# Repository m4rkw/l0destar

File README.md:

# l0destar

[l0destar.com](https://l0destar.com) A fully open-source vehicle tracker - open hardware and open software.

Inspired by the [Geolink Opentracker](https://github.com/geolink/opentracker/) and the [Fortebit Polaris](https://www.fortebit.tech/polaris/), the goal is to build something that will last: a reference design for the best possible vehicle tracker that anyone can fab, modify, and host. Hardware and software are completely open and maintained as a community project.

## Status

Prototyping / design phase. The v2.1 layout worked on a bench, and v2.6 (CAN,
K-line and micro), v3.0, v3.1, v3.2 and v3.3 have since been built and bench
tested - see the test status table in each board's README. v3.4 is designed
but not yet built or tested.

<strong>All boards before v3.3 have a serious defect in the K-wire circuit
if the L wire is connected. If any of these prototypes are built the L wire
should not be connected to the vehicle as if it was ever externally shorted
to the 12V rail the l0destar device would be damaged.</strong> Luckily very
few people are going to care at all about this ancient protocol and even fewer
will ever need the L wire in normal use but it still bears mentioning as an
indication that these are very much prototypes and there may be other
undiscovered defects.

## Disclaimer

This is a prototype, not a product. Nothing here is validated, qualified or certified, the parts lists are examples rather than a verified BOM, and any test results are my own unverified bench observations. All responsibility for anything built from it rests with the person building and installing it.

**Before building, installing or relying on any of this, read the [full disclaimer](DISCLAIMER.md).**

## What it is

- **Mission** - the world's best fully open-source vehicle tracker, no profit motive. See [`MISSION.md`](MISSION.md).
- **Goals** - KiCad reference design, open enclosure CAD, open firmware and server, weeks of standby on a typical car battery, 1 Hz GNSS, LTE-M/NB-IoT, CAN + K-Line diagnostics, accelerometer-driven wake. Full list in [`GOALS.md`](GOALS.md).
- **Technology choices** - Nordic nRF9151 SiP (LTE-M/NB-IoT + GNSS), LT8609A buck, ASM330LHHX IMU, MCP2518FD + TCAN3414 CAN, TJA1027T K-Line. Rationale and trade-offs in [`TECHNOLOGY.md`](TECHNOLOGY.md).

## License

l0destar is multi-licensed by artifact type - permissive across the board:

| Artifact | License |
|---|---|
| Hardware design files | `CERN-OHL-P-2.0` |
| Firmware | `Apache-2.0` |
| Server-side software | `Apache-2.0` |
| Documentation, enclosure CAD, media | `CC-BY-4.0` |

Full text and rationale in [`LICENSE.md`](LICENSE.md); license bodies in [`LICENSES/`](LICENSES/).

## Contributing

Contributions are welcome. l0destar uses the [Developer Certificate of Origin](https://developercertificate.org/) rather than a CLA - every commit must carry a `Signed-off-by:` trailer (`git commit -s`). See [`CONTRIBUTING.md`](CONTRIBUTING.md) for PR expectations.

## Contact

- Bug reports and feature ideas: [GitHub Issues](https://github.com/m4rkw/l0destar/issues)
- Open-ended questions and design discussion: [GitHub Discussions](https://github.com/m4rkw/l0destar/discussions)
- Direct contact: [contact me](https://l0destar.com/contact.html)

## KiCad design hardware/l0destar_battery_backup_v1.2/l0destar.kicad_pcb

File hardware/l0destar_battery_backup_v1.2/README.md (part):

# l0destar battery backup v1.2

## Overview

- This is a prototype inline battery backup module for the l0destar vehicle
  tracker. It sits in the harness between the car and the tracker and holds
  the tracker's supply at ~9V from a single CR123A lithium primary cell when
  car power is cut
- It is designed to be hand-solderable (hot air required). Every active part
  is in a leaded package: MSOP-12, SOT-23, TSOT-23, SC70, DPAK
- The cell is a **non-rechargeable** primary in a board-mounted holder.
  Nothing on the board charges it. See [Why a primary cell](#why-a-primary-cell)
- Pin-compatible with the v3.4 tracker's 2x3 Micro-Fit harness: J1 takes the
  car harness, J2 goes to the tracker, the CAN/K-line pins pass straight
  through and ignition passes through a diode (S1D1)
- 4-layer 63.1 x 36.2 mm board, JLC04161H-7628 stack-up, four M2 mounting
  holes. PCB DRC is clean and schematic ERC has only the cosmetic
  `endpoint_off_grid` warnings

## Changes from v1.1

1. External pin assignments updated for v4.0 boards

## Disclaimer

This is a prototype, not a product. Nothing here is validated or certified,
the parts lists are examples rather than a verified BOM, and every number
below is a desk calculation from datasheets rather than a bench measurement -
repeat the testing yourself rather than taking any of it on trust.

I strongly recommend not using unbranded CR123 cells or buying them from less
reputable sources.

**Before building or installing anything from this repository, read the
[full disclaimer](../../DISCLAIMER.md).**

## Test status

| Item | Test | Result | Notes |
|---------|------|--------|-------|
| Input stage | 12V car input reverse polarity | PASSED | S2Z1 conducts forward into S2F1, which should clear |
| Input stage | Pass-through drop VCAR to PPTRACKER, tracker asleep | PASSED | v1.0 dropped ~0.5V here. Expected ~20 mV, the LTC4412 regulated forward drop |
| Input stage | Pass-through drop VCAR to PPTRACKER at 50 mA and 250 mA | PASSED | Expected ~20 mV; S2Q1 is 15 mΩ so the regulation sets it, not R<sub>DS(on)</sub> |
| Switchover | Boost enables when the car rail falls below ~10.06V | PASSED | S6U1 with the 6.8M/909k divider |
| Switchover | Boost disables when the car rail returns above ~11V | PASSED | Depends on the cell voltage through S6R38/S6R39, see [Notes](#notes) |
| Boost | 9.6V output at S4C14/S4C15 | PASSED | 1.202V x (1 + 909k/130k) = 9.61V; ~9V at J2 after S2D2 |
| Cell | Reversed cell is harmless | PASSED | Not physically possible to install the cell backwards |
| Cell | No current ever flows into the cell | PASSED | Ammeter in series with the cell with the car present and during handover |
| Wake pulse | IGN pulse at boost start, car ignition wire connected and off | PASSED | Failed on v1.0. Expected ~12V peak, above 8V for ~0.4 s, at J2 pin 5, with S1D1 blocking the car pulldown |
| Wake pulse | Car ignition reaches the tracker | PASSED | J2 pin 5 should be one S1B drop below J1 pin 5 with the key on |
| Wake pulse | Sleeping tracker wakes and raises `backup power` | PASSED | Needs firmware with `CONFIG_APP_BACKUP_SUPPLY=y` |
| Board | Parked drain from the car with the cell fitted | PASSED | ~15 µA on top of the tracker's own draw |

## Features

 - Inline between the car harness and the tracker; CAN/K-line pass straight
   through, ignition through S1D1
 - ~15 µA quiescent draw from the car in pass-through: ~13 µA LTC4412HV plus
   the ~1.6 µA sense divider
 - Same input protection parts as the tracker: 2A time-lag fuse, 33V TVS
   sized to ride out suppressed load dump
 - Reverse polarity protection
 - Ideal diode pass-through (LTC4412HV + P-channel FET) with a ~20 mV drop
   down to sleep current
 - Synchronous boost (LTC3122) with true output disconnect: the backup rail
   is 0V while the car is present, so the cell is only ever loaded during a
   cut
 - Nanopower comparator switchover (TLV3012, 2.8 µA) running straight from
   the cell: takes over below ~10.06V on the car rail
 - No cell lockout: the boost runs the cell until it can't. It's a
   consumable primary, so there is nothing to protect
 - Ignition wake pulse: a cut wakes a sleeping tracker immediately instead of
   at its next timed wake, and the tracker reports the cut
 - Estimated runtime on a 1500 mAh CR123A: ~200 days idle, ~58 days
   reporting hourly, ~19 days reporting every 15 minutes
 - 3D-printable two-part enclosure with the cell accessible under the lid

## Why a primary cell

A non-rechargeable cell rather than a rechargeable pack, for three reasons:

- No rechargeable 18650-format cell is rated for storage in a sun-parked car.
  The binding limit is storage temperature (+45 °C at best for Li-ion and LFP;
  +20 °C beyond three months for LTO) and a parked car reaches ~70 °C cabin
  air. A CR123A is rated to +60/+70 °C
- Cycle life is not worth paying for. The backup cycles a handful of times a
  year
- A primary turns silent ageing into an event. The boost regulates its output,
  so the tracker cannot see cell voltage - a rechargeable's calendar fade would
  be invisible until a real theft tested it. The only thing that consumes a
  primary is a power cut the tracker already alerts on, so *"did it get
  used?"* is answered in the server's alert log

The cell is a consumable. A `backup power` alert that runs for a long time
means the cell needs replacing, since it does not recover. Taking the cell
out is the storage mode.

### Ignition wake pulse

A sleeping tracker has three wake sources: its timer, the accelerometer and
ignition-present. A power cut touches none of them, so on its own it would be
found at the next timed wake. The module therefore fakes ignition for a
moment when it takes over.

The tracker's wake is level-triggered and the firmware latches it, so the
pulse only has to trip the interrupt. On an ignition wake the firmware reads
the rail first: in the backup band it is the module's pulse, so the unit
reports at once with the `backup power` alert and goes back to sleep.

The car holds its ignition wire at ground when the key is off, which sank
the pulse on v1.0. S1D1 sits in series between the car's ignition (J1 pin 5)
and the tracker's (J2 pin 5) so the pulse only drives the tracker's input.
The cost is one silicon diode drop on the ignition signal the tracker sees.

Limits: a second cut within the ~40 s VBOOST decay gives no pulse and falls
back to the timed wake.

## Board configuration

### Connectors

Both connectors are the tracker's Molex Micro-Fit 3.0 2x3 (43045-0600) with
the v3.4 pinout. J1 is the car harness, J2 goes to the tracker.

| Pin | J1 (car) | J2 (tracker) | Notes |
|-----|----------|--------------|-------|
| 1 | SPARE | SPARE | Unused by v3.4, not connected on this board |
| 2 | GND | GND | |
| 3 | CAN\_H / K | CAN\_H / K | Passed straight through |
| 4 | +12V | +12V (PPTRACKER) | Car through the ideal diode, or ~9V from the boost on backup |
| 5 | IGN | IGN | Through S1D1 (one diode drop); the wake pulse is injected on the J2 side |
| 6 | CAN\_L / L | CAN\_L / L | Passed straight through |

### Firmware

The tracker needs `CONFIG_APP_BACKUP_SUPPLY=y`. With it, a supply between
`CONFIG_APP_BACKUP_MIN_MV` (8500) and `CONFIG_APP_BACKUP_MAX_MV` (9700) with
the ignition off is treated as backup power rather than a flat car battery:
timed reports keep going, the 11.8V power-off and 12.0V sleep-safety rules
are bypassed, a `backup power` alert is raised once and a `car power
restored` alert when the rail comes back. Without the module a car battery in
that band is flat, so leave it off on trackers that do not have one.

### Cell

The board carries a Keystone 1051 CR123A holder and nothing else as a cell
input. Fit a CR123A from one of the three big brands (Energizer 123 /
EL123AP, Panasonic CR123A, Duracell DL123A): all are high-rate Li-MnO2 cells,
1500-1550 mAh, rated for the ~130 mA typical / ~250 mA worst-case bursts the
boost draws. Mark polarity on the silk and the lid; a reversed cell is
harmless but gives no backup.

Other primary chemistries (a 4.1V Tadiran TLM for installs above 60 °C, a
C-size Li-SOCl2 for long runtime) are **not** stuffing options on this board:
neither fits the CR123A holder, a 4.1V cell needs the comparator's supply
range and the boost input checked, and Li-SOCl2 wants a depassivation
bleed. Either is a sheet 3 change.

## Notes

 - **Nothing may ever charge the cell.** Do not add any path from VBOOST,
   PPTRACKER or VCAR to VBAT. If the LM66100 is ever replaced, the
   replacement must block reverse current
 - The LTC3122's exposed pad is PGND. Solder it
 - The tracker's flex-crack rule applies to every 1210 ceramic on this board
   (S2C5, S2C6, S4C14, S4C15): soft-termination parts only, kept away from
   board edges and mounting holes
 - S4R19 (boost FB top) is the one anti-sulfur resistor that matters: open, the
   LTC3122 runs to its ceiling, the same failure as the tracker buck's top
   resistor. S6R33 uses the same part for convenience. Everything else is
   plain thick film; use a non-sulfur foam under the lid over the cell
 - S2D2 and S5D3 must stay glass-passivated silicon (S1B), not Schottky. The
   wake pulse depends on VBOOST resting near 0V while the car is present, and
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
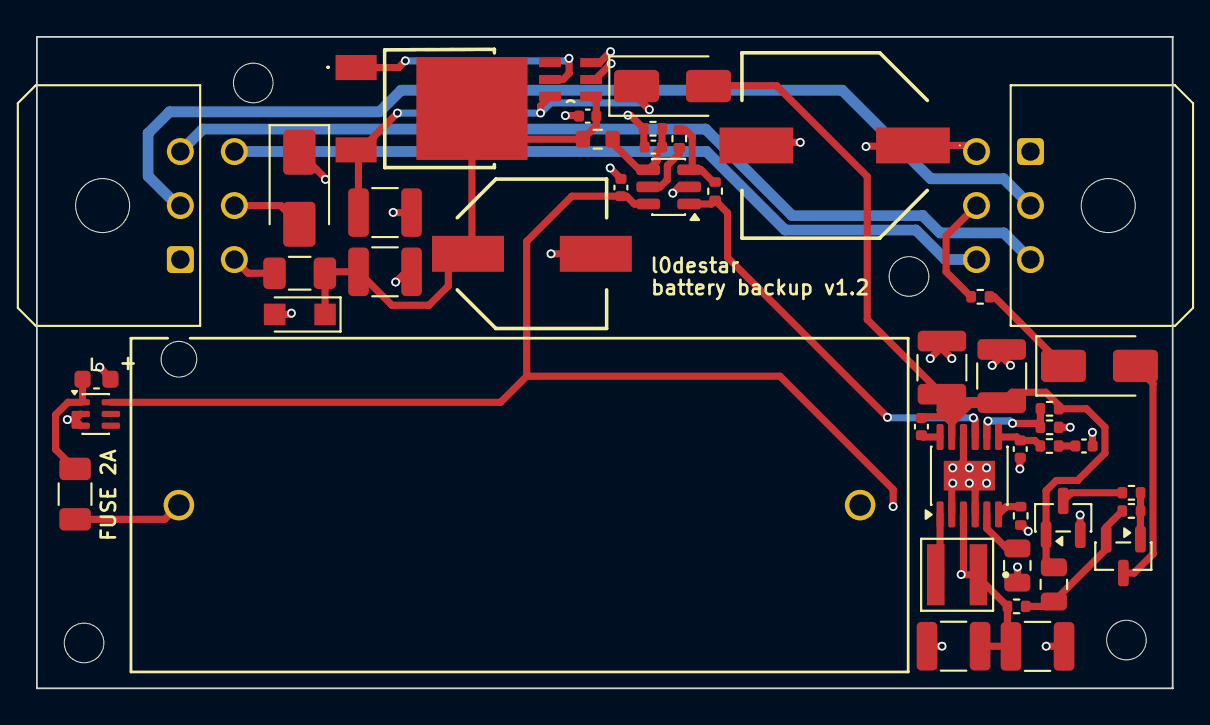
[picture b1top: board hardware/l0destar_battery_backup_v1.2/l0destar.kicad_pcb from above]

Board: 4 copper layers, 63.1 x 36.2 mm, 50 parts (0 on the bottom side), 30 nets.

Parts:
S1D1, S2D2, S5D3: S1B; D_SMA
S1H1, S1H2, S1H3, S1H4: MountingHole; MountingHole_2.2mm_M2
S1J1: Car harness; Molex_Micro-Fit_3.0_43045-0600_2x03_P3.00mm_Horizontal
S1J2: Tracker harness; Molex_Micro-Fit_3.0_43045-0600_2x03_P3.00mm_Horizontal
S2C1, S4C9, S6C2: 0402 100nF 50V 10% X7R; C_0402_1005Metric
S2C2: 47uF 63V - EEH-ZC1J470P; EEH_ZC1J470P
S2C4: 82uF 63V - HHXC630ARA820MJA0G; HHXC630ARA820MJA0G
S2C5, S2C6, S4C14, S4C15: 1210 10uF 50V X7R SOFT-TERM; C_1210_3225Metric
S2F1, S3F1: 0407002.WRA; Fuse_1206_3216Metric
S2Q1: SQD50P06-15L_GE3; SQD50P06-15L_GE3_tight
S2U1: LTC4412HVIS6PBF
S2Z1: PTVS33VS1UTR,115; Nexperia_CFP3_SOD-123W
S3BT1: CR123A; 1051_KEY
S3C1: 0603 2.2uF 25V 10% X7R; C_0603_1608Metric
S3U1: LM66100DCKR; SOT-363_SC-70-6
S4C7, S4C8: 1210 47uF 10V 20% X7R; C_1210_3225Metric
S4C11: 0402 560pF 50V 5% C0G/NP0; C_0402_1005Metric
S4C12: 0402 10pF 50V C0G/NP0; C_0402_1005Metric
S4C13, S5C17: 0805 4.7uF 50V 10% X7R; C_0805_2012Metric
S4L1: 2.2uH XFL4020-222MEC; IND_XFL4020-222ME
S4R14: 0402 57.6K 1%; R_0402_1005Metric
S4R18: 0402 200K 1%; R_0402_1005Metric
S4R19, S6R33: 0402 909K 1% ANTI-SULFUR AEC-Q200; R_0402_1005Metric
S4R20: 0402 130K 1%; R_0402_1005Metric
S4U5: LTC3122EMSE#PBF; MSOP-12-1EP_3x4.039mm_P0.65mm_EP1.651x2.845mm
S5Q6: 2N7002; SOT-23
S5Q7: BC856B; SOT-23
S5R21: 0402 10K 5%; R_0402_1005Metric
S5R22, S5R24, S5R25, S6R39: 0402 1M 1%; R_0402_1005Metric
S6C1: 0402 100pF 50V 5% C0G/NP0; C_0402_1005Metric
S6R32: 0603 6.8M 1%; R_0603_1608Metric
S6R38: 0402 47K 5%; R_0402_1005Metric
S6U1: TLV3012AIDBVR; SOT-23-6

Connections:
CAN_H: S1J1.3, S1J2.3
CAN_L: S1J1.6, S1J2.6
EN_BOOST: S4U5.9 (SD), S6R39.1, S6U1.1 (OUT)
GND: S1J1.1, S1J2.1, S2C1.2, S2C2.2 (-), S2C4.2 (-), S2C5.2, S2C6.2, S2U1.2 (GND), S2U1.3 (CTL), S2Z1.2 (A), S3BT1.2, S3C1.2, S3U1.2 (GND), S3U1.3 (~CE), S4C7.2, S4C8.2, S4C11.2, S4C12.2, S4C13.2, S4C14.2, S4C15.2, S4R14.2, S4R20.2, S4U5.2 (PGND), S4U5.4 (PWM/SYNC), S4U5.10 (SGND), S4U5.13 (EP), S5Q6.2 (S), S6C1.2, S6C2.2, S6R33.2, S6U1.2 (V-)
IGN: S1D1.1 (K), S1J2.5, S5R21.2
IGN_CAR: S1D1.2 (A), S1J1.5
KWIRE_K: S1J1.2, S1J2.2
unnamed: S2Q1.1 (G), S2U1.5 (GATE)
unnamed: S3BT1.1, S3F1.1
unnamed: S3C1.1, S3F1.2, S3U1.1 (VIN)
unnamed: S4C11.1, S4R18.2
unnamed: S4C9.1, S4U5.12 (CAP)
unnamed: S4R19.2, S4R20.1, S4U5.8 (FB)
unnamed: S4R14.1, S4U5.6 (RT)
unnamed: S4L1.2, S4U5.1 (SW)
unnamed: S4C12.1, S4R18.1, S4U5.7 (VC)
unnamed: S4C13.1, S4U5.5 (VCC)
unnamed: S5D3.2 (A), S5Q7.3 (C)
unnamed: S5D3.1 (K), S5R21.1
unnamed: S5Q6.3 (D), S5R24.2
unnamed: S5Q7.1 (B), S5R24.1, S5R25.2
unnamed: S5C17.1, S5Q7.2 (E), S5R22.2, S5R25.1
unnamed: S6R38.2, S6R39.2, S6U1.3 (IN+)
unnamed: S6C1.1, S6R32.2, S6R33.1, S6U1.4 (IN-)
unnamed: S6R38.1, S6U1.5 (REF)
PP12V: S1J1.4, S2F1.1
PPTRACKER: S1J2.4, S2C4.1 (+), S2C5.1, S2D2.1 (K), S2Q1.3 (S), S2U1.6 (SENSE)
VBAT: S3U1.6 (VOUT), S4C7.1, S4C8.1, S4L1.1, S4U5.3 (VIN), S5R22.1, S6C2.1, S6U1.6 (V+)
VBOOST: S2D2.2 (A), S4C9.2, S4C14.1, S4C15.1, S4R19.1, S4U5.11 (VOUT), S5C17.2, S5Q6.1 (G)
VCAR: S2C1.1, S2C2.1 (+), S2C6.1, S2F1.2, S2Q1.2 (D), S2U1.1 (VIN), S2Z1.1 (K), S6R32.1

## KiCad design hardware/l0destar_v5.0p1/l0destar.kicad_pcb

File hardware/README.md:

# l0destar hardware

**Before building, installing or relying on any of this, read the [project disclaimer](../DISCLAIMER.md).**

## Overview

KiCad PCB designs for the l0destar vehicle tracker. All boards are built around
the Nordic nRF9151 for LTE-M/GPS and share a common set of subsystems: 12V
automotive power input, INA228 voltage monitoring, ignition sensing, and an
accelerometer/IMU.

**THESE SHOULD NOT BE CONSIDERED FINISHED PRODUCTS. SOME OF THEM HAVEN'T BEEN
TESTED AT ALL. USE ENTIRELY AT YOUR OWN RISK.**

**SOME OF THESE HAVE KNOWN DEFECTS DETAILED IN THEIR README**

Prototypes here are currently being tested and evaluated, there are typically a
few in the pipeline at any given time. Older boards no longer being tested are
moved into the [archive](archive/).

## PCB designs

### v3.1 - input resilience, hardened antenna feed, aux rail fault detection

- **[l0destar v3.1](l0destar_v3.1/)** - v3.0 with more robust input protection
  (sized for ISO 7637-2 pulse 2a), auxiliary power rail sensing/fault
  detection, and a hardened antenna feed with 15R series resistance and ESD
  protection. Same footprint as v3.0. Tested - 130 µA quiescent, all major
  subsystems passed.

### v3.2 - MCU over-voltage protection

- **[l0destar v3.2](l0destar_v3.2/)** - v3.1 plus hardware over-voltage
  protection that disconnects the module supply within microseconds of a
  regulator fault (self-recovering, no firmware dependency, ~10 µA), and I2C
  bus hardening against LTE TX bursts (stronger pull-ups, 100pF filter caps
  on SDA/SCL, series jumper/ferrite on the accelerometer supply).

  Tested successfully: <a href="https://www.youtube.com/watch?v=6-iVvQPaaeg">OVP scope test</a>.
  134 µA quiescent with firmware 0.4.26 (140.8 µA before it moved the sleep
  wake interrupts off the GPIOTE channels).

### v3.3 - L-line defect fix

- **[l0destar v3.3](l0destar_v3.3/)** - fixes the L-line short-to-battery
  defect present in v3.0-v3.2 (pulldown current limited to 90 mA via an
  AL5809-90, gate-fault current into the nRF limited) and adds L-line fault
  sensing so a 12V short can be detected. Buck converter tuned to shut off
  cleanly below ~4.3V and restart only above ~5.6V to avoid flapping. Built and
  bench tested: 146.2 µA quiescent as built, 43.7 µA with the accelerometer's
  NC pads scraped off.

### v3.4 - accelerometer fix

- **[l0destar v3.4](l0destar_v3.4/)** - v3.3 with the accelerometer's NC pins
  left unconnected (grounded on v3.0-v3.3, which kept the part out of its
  low-power state), the buck enable divider made optional, test points added
  and a TCAN3414DR CAN transceiver specified. Not yet built or tested; ~35.5 µA
  quiescent expected at 12V.

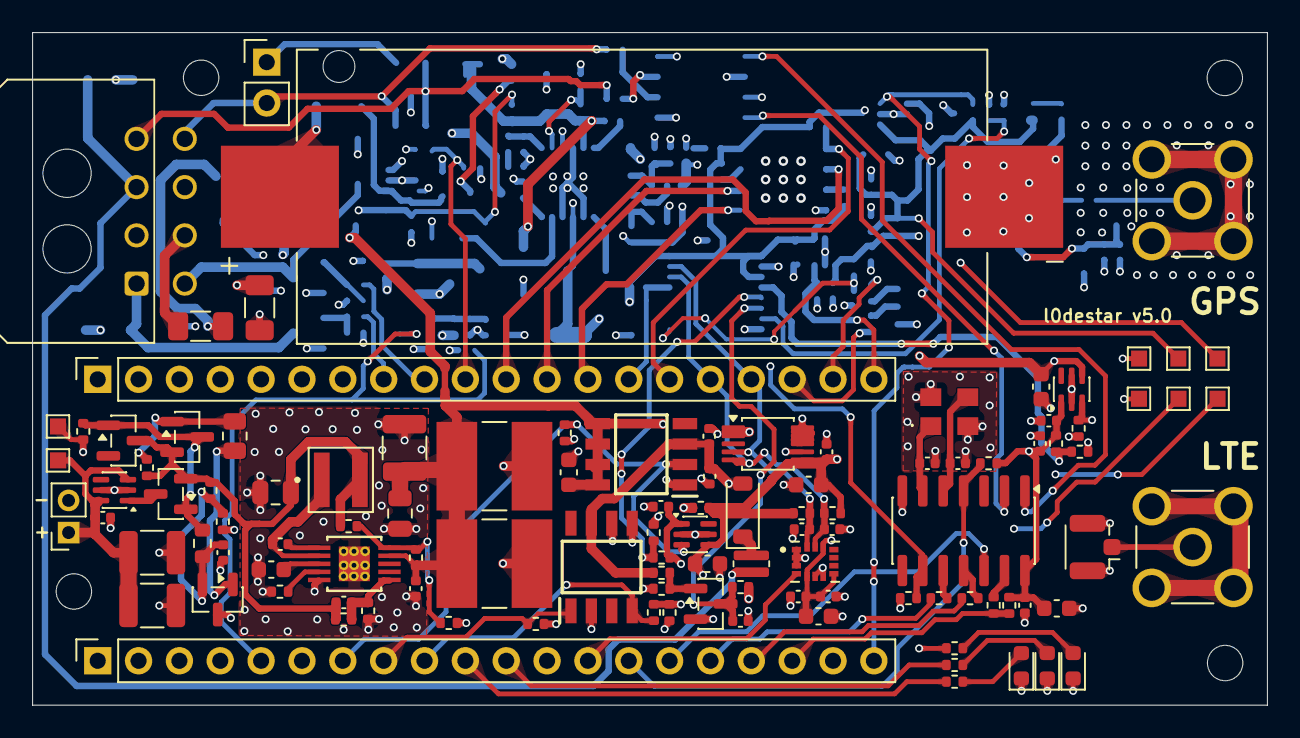
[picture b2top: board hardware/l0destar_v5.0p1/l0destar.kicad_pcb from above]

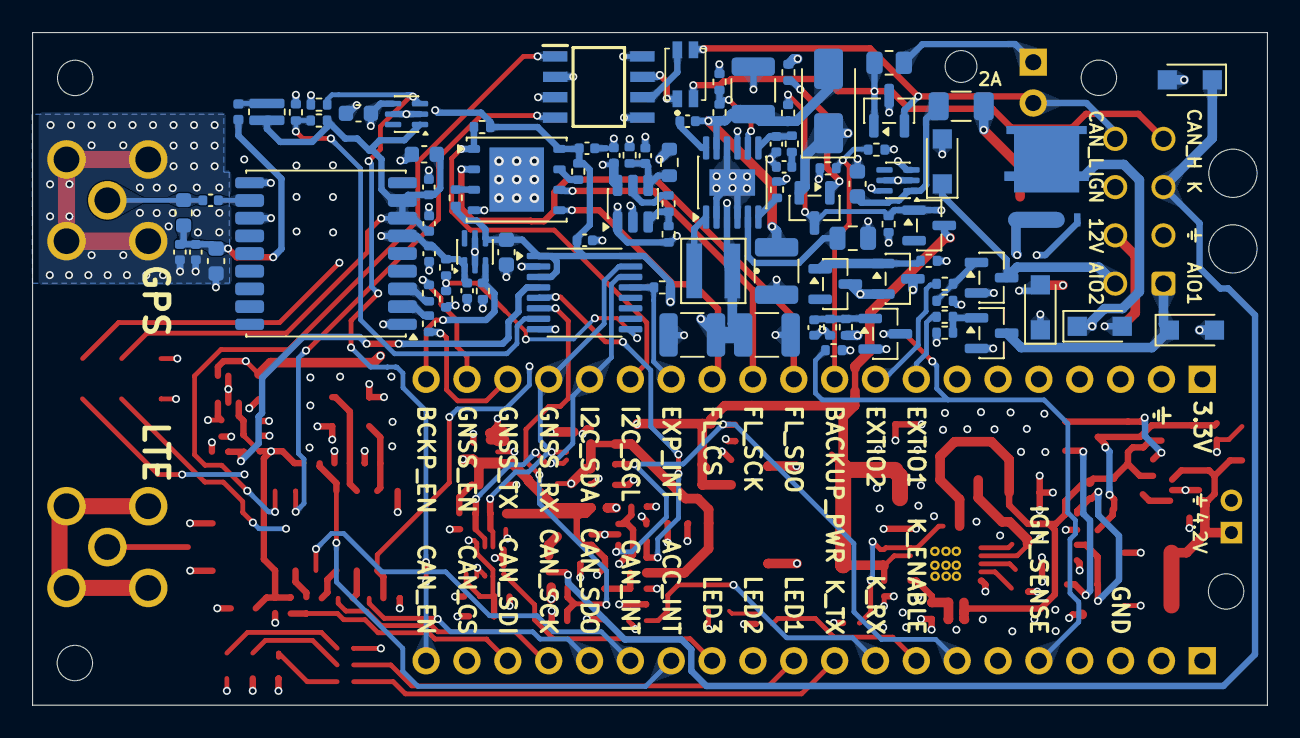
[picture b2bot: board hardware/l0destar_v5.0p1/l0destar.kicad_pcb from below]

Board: 4 copper layers, 76.8 x 41.8 mm, 202 parts (89 on the bottom side), 112 nets.

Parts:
H1, H2, H3, H4: MountingHole; MountingHole_2.2mm_M2
S1C1, S3C2, S4C1, S6C1, S6C8, S7C2, S7C4, S7C9, S8C1, S8C3, S9C1, S9C4, S10C1, S16C2, S16C4, S16C5, S17C1, S19C9, S20C2, S22C1: 0402 100nF 50V 10% X7R; C_0402_1005Metric
S1J1: Main connector; Molex_Micro-Fit_3.0_43045-0800_2x04_P3.00mm_Horizontal
S1J2: Conn_01x20_Socket; MakerDiary_nRF9151_ConnectKit_PinHeader_1-20_tight
S1J3: Conn_01x20_Socket_21-40; MakerDiary_nRF9151_ConnectKit_PinHeader_21-40_tight
S1J4: +; MakerDiary2PinHeader
S1R1, S1R2: 0402 1.8K 1%; R_0402_1005Metric
S1R3, S1R4, S1R5, S2R3, S2R4, S7R3, S7R6, S7R7, S7R8, S7R10, S10R6, S16R1, S16R4, S21R2, S21R4: 0402 100K 5%; R_0402_1005Metric
S2C1, S2C2: 47uF 2220 50V 20% X7R; CAPC6050X550N
S2C3: 10uF 1210 50V 10% X7R SOFT TERMINATION; C_1210_3225Metric
S2D1, S2D3, S11D1: BZX84C15; SOT-23
S2D2, S2D4, S10D2, S21D1, S21D2: PTVS33VS1UTR,115; Nexperia_CFP3_SOD-123W
S2D5: S1B; D_SMA
S2F1, S2F2, S18F1: 0407002.WRA; Fuse_1206_3216Metric
S2Q1, S2Q3, S11Q1: SQ2361CES-T1_BE3; SOT-23
S2Q2: SQJ457EP-T1_BE3; POWERPAK-SO-8-4
S2R1, S7R4, S7R9, S7R11, S16R5: 0402 1M 5%; R_0402_1005Metric
S2R2, S20R41: 0402 2.2M 1%; R_0402_1005Metric
S3C1, S6C2, S7C1, S7C3, S7C8, S15C4, S16C1, S16C3, S18C1: 0603 2.2uF 25V 10% X7R; C_0603_1608Metric
S3U1: INA238; TSSOP-10_3x3mm_P0.5mm
S4Q1, S7Q1, S21Q1, S21Q2: 2N7002; SOT-23
S4R1, S7R5: 0402 180K 5%; R_0402_1005Metric
S4R2, S4R3: 0402 56K 5%; R_0402_1005Metric
S6C3, S19C13: 0805 4.7uF 50V 10% X7R; C_0805_2012Metric
S6C4, S19C12: 0402 10pF 50V C0G/NP0; C_0402_1005Metric
S6C5: 0805 22uF 10V 20% X7R; C_0805_2012Metric
S6L1: XFL4020-222ME; IND_XFL4020-222ME
S6R1: 0402 18.2K 1%; R_0402_1005Metric
S6R2: 0402 226K 1% ANTI-SULFUR AEC-Q200; R_0402_1005Metric
S6R3, S11R5: 0402 1M 1% ANTI-SULFUR AEC-Q200; R_0402_1005Metric
S6R4: 0402 0R JUMPER OR 1M 1% ANTI-SULFUR AEC-Q200; R_0402_1005Metric
S6R5: DNP 0402 243K 1% ANTI-SULFUR AEC-Q200; R_0402_1005Metric
S6R6: DNP 0402 3.92M 1%; R_0402_1005Metric
S6U1: LT8609AIMSE_PBF; LT8609AIMSE_WITH_GROUND_VIAS
S7C5, S7C7: 0402 1nF 50V 10% X7R; C_0402_1005Metric
S7C6: 0603 220nF 50V 10% X7R; C_0603_1608Metric
S7U1, S7U2, S7U4, S16U1: SiP32431DR3; SOT-363_SC-70-6
S7U3: ITS4060SSJNXUMA1
S8C2, S9C5: 0603 10uF 10V 20% X7R; C_0603_1608Metric
S8C4, S8C5, S15C2, S20C1: 0402 100pF 50V 5% C0G/NP0; C_0402_1005Metric
S8R1: 0402 FB BLM15AG601SH1D; R_0402_1005Metric
S8U1: ASM330LHHXTR; XDCR_ASM330LHHXTR
S9C2, S9C3: 0402 27pF 10V 5% C0G/NP0; C_0402_1005Metric
S9D1: NUP2105L; SOT-23
S9FL1: ACT1210-101-2P-TL00; ACT12101012PTL00_tight
S9J1: Conn_01x02_Pin; PinHeader_1x02_P2.54mm_Vertical_Tight
S9R1, S9R2, S9R4, S10R1, S10R2, S17R1, S17R2, S17R3, S20R40, S22R1: 0402 10K 5%; R_0402_1005Metric
S9R3: 0805 120R 5% 0.5W; R_0805_2012Metric
S9R5, S13R1, S13R2, S13R3, S16R2, S16R3, S21R1, S21R3: 0402 1K 5%; R_0402_1005Metric
S9R6, S9R7: 0402 220R 5%; R_0402_1005Metric
S9U1: TCAN3414DR; SOIC127P600X175-8N
S9U2: MCP2518FD-xQBB; SOIC-14_3.9x8.7mm_P1.27mm
S9Y1: ECS-400-18-33-JGN-TR3; ECS4001833JGNTR3
S10D1: 1N4148W; D_SOD-123
S10R3: 0508 510R 5% 1W; R_0508_1220Metric_WideTerminal_Tight
S10U1: TJA1027T_20,118; TJA1027T_20_118
S11C1, S11C2, S19C7, S19C8: 1210 47uF 10V 20% X7R; C_1210_3225Metric
S11C3: 0402 3.3pF 50V C0G/NP0 +/- 0.25pF; C_0402_1005Metric
S11Q2: BC856BLT1G; SOT-23
S11R1: 0402 10K 1%; R_0402_1005Metric
S11R2, S20R39: 0402 1M 1%; R_0402_1005Metric
S11R3: 0603 33M 5%; R_0603_1608Metric
S11R4: 0805 15K 1% ANTI-SULFUR AEC-Q200; R_0805_2012Metric
S11R6: 0402 1.05M 1%; R_0402_1005Metric
S11U1: LM66100DCK; SOT-363_SC-70-6
S11U2: ATL431BQDBZR; SOT-23
S12TP1: GND; TestPoint_Pad_1.0x1.0mm
S12TP2: 4.2V protected; TestPoint_Pad_1.0x1.0mm
S12TP3: 3.3V; TestPoint_Pad_1.0x1.0mm
S12TP4: 3.3V GNSS BCKP; TestPoint_Pad_1.0x1.0mm
S12TP5: 3.3V CAN; TestPoint_Pad_1.0x1.0mm
S12TP6: 3.3V K; TestPoint_Pad_1.0x1.0mm
S12TP7: 12V K; TestPoint_Pad_1.0x1.0mm
S13D1, S13D2, S13D3: Wurth 150060RS86000; LED_0603_1608Metric
S15C1: 0402 47pF 50V 5% C0G/NP0; C_0402_1005Metric
S15C3: 0402 10nF 50V 5% C0G/NP0; C_0402_1005Metric
S15FB1: 0402 600R 0.5A 25%; L_0402_1005Metric
S15J2: GPS_SMA; SAMTEC_SMA-J-P-H-RA-TH1_centrepin
S15J3: GSM_UFL; U.FL_Hirose_U.FL-R-SMT-1_Vertical
S15J4: GSM_SMA; SAMTEC_SMA-J-P-H-RA-TH1_centrepin
S15L1: LQW18AN68NJ00D; L_0603_1608Metric
S15R1: 0508 1W 5% 15R; R_0508_1220Metric_WideTerminal_Tight
S16TP1: 3.3V GNSS; TestPoint_Pad_1.0x1.0mm
S16U2: MAX-M10S; ublox_MAX
S17U1: MX25R6435FZNIL0; WSON-8-1EP_6x5mm_P1.27mm_EP3.4x4mm_no_vias
S18BT1: CR123A; 1050
S18U1: LM66100DCKR; SOT-363_SC-70-6
S19C11: 0402 560pF 50V 5% C0G/NP0; C_0402_1005Metric
S19C14, S19C15: 1210 10uF 50V X7R SOFT-TERM; C_1210_3225Metric
S19L1: 2.2uH XFL4020-222MEC; IND_XFL4020-222ME
S19R14: 0402 57.6K 1%; R_0402_1005Metric
S19R18: 0402 200K 1%; R_0402_1005Metric
S19R19, S20R33: 0402 909K 1% ANTI-SULFUR AEC-Q200; R_0402_1005Metric
S19R20: 0402 130K 1%; R_0402_1005Metric
S19U5: LTC3122EMSE#PBF; MSOP-12-1EP_3x4.039mm_P0.65mm_EP1.651x2.845mm
S20R32: 0603 6.8M 1%; R_0603_1608Metric
S20R38: 0402 47K 5%; R_0402_1005Metric
S20U1: TLV3012AIDBVR; SOT-23-6
S22U1: TCA6408APWR; TSSOP-16_4.4x5mm_P0.65mm

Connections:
/FLASH_RESET: S17R3.2, S17U1.7 (~RESET/SIO3)
/FLASH_WP: S17R2.2, S17U1.3 (~WP/SIO2)
/S2_GATE: S2D3.1 (A), S2Q2.4, S2Q3.3 (D), S2R2.1, S2R4.2
ACCELL_INT1: S1J2.13, S8U1.4 (INT1)
AIO1: S1J1.1, S21D1.1 (K), S21Q1.3 (D)
AIO2: S1J1.5, S21D2.1 (K), S21Q2.3 (D)
BACKUP_PWR: S1J3.31 (Pin_10), S20R40.2, S20R41.1
CAN_CS: S1J2.18, S9R1.2, S9R5.1
CAN_ENABLE: S1J2.19, S1R4.2, S7U2.3 (ON)
CAN_H: S1J1.4, S9D1.1 (K), S9FL1.2, S9R3.2
CAN_INT: S1J2.14, S9R2.2, S9U2.4 (~INT)
CAN_L: S1J1.8, S9D1.2 (K), S9FL1.3, S9J1.2
CAN_SCK: S1J2.16, S9R6.1
CAN_SDI: S1J2.17, S9R7.1
CAN_SDO: S1J2.15, S9U2.12 (SDO)
EN_BOOST: S19U5.9 (SD), S20R39.1, S20R40.1, S20U1.1 (OUT)
EXP_INT: S1J3.27 (Pin_14), S22R1.2, S22U1.13 (~INT)
EXTIO1: S1J3.33 (Pin_8), S21R1.1
EXTIO2: S1J3.32 (Pin_9), S21R3.1
FLASH_CS: S1J3.26 (Pin_15), S17R1.2, S17U1.1 (~CS)
FLASH_SCK: S1J3.29 (Pin_12), S17U1.6 (SCLK)
FLASH_SDI: S1J3.28 (Pin_13), S17U1.5 (SI/SIO0)
FLASH_SDO: S1J3.30 (Pin_11), S17U1.2 (SO/SIO1)
GND: S1C1.1, S1J1.2, S1J2.3 (GND), S1J3.39 (Pin_2), S1J4.2, S1R3.1, S1R4.1, S1R5.1, S2C1.2, S2C2.2, S2C3.2, S2D2.2 (A), S2D4.2 (A), S2R1.2, S2R2.2, S3C1.1, S3C2.1, S3U1.1 (A1), S3U1.2 (A0), S3U1.7 (GND), S4C1.2, S4Q1.2 (S), S4R2.1, S6C2.2, S6C3.2, S6C5.2, S6C8.2, S6R1.2, S6R2.2, S6R5.1, S6U1.5 (SYNC), S6U1.11 (GND), S7C1.2, S7C2.2, S7C3.2, S7C4.2, S7C5.2, S7C6.2, S7C7.2, S7C8.2, S7C9.2, S7Q1.2 (S), S7R4.1, S7R6.1, S7R9.1, S7R11.1, S7U1.2 (GND), S7U1.5 (GND), S7U2.2 (GND), S7U2.5 (GND), S7U3.1 (GND), S7U4.2 (GND), S7U4.5 (GND), S8C1.2, S8C2.2, S8C3.2, S8C4.2, S8C5.2, S8U1.1 (SDO/SA0), S8U1.2 (MSDA), S8U1.3 (MSCL), S8U1.6 (NC), S8U1.7 (GND), S9C1.2, S9C2.2, S9C3.2, S9C4.2, S9C5.2, S9D1.3 (A), S9R4.2, S9U1.2 (GND), S9U1.5 (SHDN), S9U2.7 (VSS), S9Y1.2 (GND_1), S9Y1.4 (GND_2), S10C1.1, S10D2.2 (A), S10U1.5 (GND), S11C1.2, S11C2.2, S11C3.1, S11R2.1, S11R6.1, S11U1.2 (GND), S11U1.5 (ST), S11U2.3 (ANODE), S12TP1.1 (1_1), S13D1.1 (K), S13D2.1 (K), S13D3.1 (K), S15C2.2, S15C3.2, S15C4.2, S15J2.2, S15J2.3, S15J2.4, S15J2.5, S15J3.2 (Ext), S15J4.2, S15J4.3, S15J4.4, S15J4.5, S16C1.2, S16C2.2, S16C3.2, S16C4.2, S16C5.2, S16R1.2, S16R5.2, S16U1.2 (GND), S16U1.5 (GND), S16U2.1 (GND), S16U2.10 (GND), S16U2.12 (GND), S17C1.2, S17U1.4 (GND), S17U1.9 (GND), S18BT1.N, S18C1.2, S18U1.2 (GND), S18U1.5 (ST), S19C7.2, S19C8.2, S19C11.2, S19C12.2, S19C13.2, S19C14.2, S19C15.2, S19R14.2, S19R20.2, S19U5.2 (PGND), S19U5.4 (PWM/SYNC), S19U5.10 (SGND), S19U5.13 (EP), S20C1.2, S20C2.2, S20R33.2, S20R41.2, S20U1.2 (V-), S21D1.2 (A), S21D2.2 (A), S21Q1.2 (S), S21Q2.2 (S), S21R2.2, S21R4.2, S22C1.2, S22U1.2 (ADDR), S22U1.8 (GND)
GNSS_BCKP_EN: S1J3.21 (Pin_20), S1R3.2, S7U1.3 (ON)
GNSS_ENABLE: S1J2.20, S16R1.1, S16U1.3 (ON)
GNSS_RF: S15C1.1, S16U2.11 (RF_IN)
GNSS_RX: S1J3.23 (Pin_18), S16R2.1
GNSS_TX: S1J3.22 (Pin_19), S16R3.1
I2C_SCL: S1J3.25 (Pin_16), S1R2.1, S3U1.5 (SCL), S8C5.1, S8U1.13 (SCL), S22U1.14 (SCL)
I2C_SDA: S1J3.24 (Pin_17), S1R1.1, S3U1.4 (SDA), S8C4.1, S8U1.14 (SDA), S22U1.15 (SDA)
IGN_SENSE: S1J2.5 (P9), S4Q1.3 (D), S4R3.2
KWIRE_K: S1J1.3, S10D2.1 (K), S10R3.2, S10U1.6 (LIN)
K_ENABLE: S1J2.7, S1R5.2, S7U3.2 (IN), S7U4.3 (ON)
K_RX: S1J2.8, S10R1.2, S10U1.1 (RXD)
K_TX: S1J2.9, S10R2.2, S10U1.4 (TXD)
LED1: S1J2.10, S13R1.2
LED2: S1J2.11, S13R2.2
LED3: S1J2.12, S13R3.2
unnamed: S2D1.1 (A), S2Q1.1 (G), S2R1.1
unnamed: S2D2.1 (K), S2F1.1, S2Q1.3 (D)
unnamed: S2D4.1 (K), S2F2.2, S2Q2.5_0, S2Q2.5_1, S2Q2.5_2, S2Q2.5_3
unnamed: S2Q3.1 (G), S2R3.1
unnamed: S4C1.1, S4Q1.1 (G), S4R1.2, S4R2.2
unnamed: S6C1.1, S6U1.1 (BST)
unnamed: S6R4.1, S6R5.2, S6R6.2, S6U1.10 (EN/UV)
unnamed: S6C4.1, S6R2.1, S6R3.1, S6U1.6 (FB)
unnamed: S6C2.1, S6U1.3 (INTVCC)
unnamed: S6R1.1, S6U1.4 (RT)
unnamed: S6C1.2, S6L1.1, S6U1.2 (SW)
unnamed: S7Q1.1 (G), S7R5.2, S7R6.2
unnamed: S8C1.1, S8C2.1, S8C3.1, S8R1.2, S8U1.5 (VDD_IO), S8U1.8 (VDD), S8U1.12 (CS)
unnamed: S9J1.1, S9R3.1
unnamed: S9FL1.1, S9U1.7 (CANH)
unnamed: S9FL1.4, S9U1.6 (CANL)
unnamed: S9U1.4 (RXD), S9U2.2 (RXCAN)
unnamed: S9R4.1, S9U1.8 (STBY), S9U2.9 (~INT0/GPIO0/XSTBY)
unnamed: S9U1.1 (TXD), S9U2.1 (TXCAN)
unnamed: S9C3.1, S9U2.6 (OSC1), S9Y1.1 (IN/OUT)
unnamed: S9C2.1, S9U2.5 (OSC2), S9Y1.3 (OUT/IN)
unnamed: S9R6.2, S9U2.10 (SCK)
unnamed: S9R7.2, S9U2.11 (SDI)
unnamed: S9R5.2, S9U2.13 (~CS)
unnamed: S10D1.1 (K), S10R3.1
unnamed: S10R6.1, S10U1.2 (SLP_N)
unnamed: S11D1.1 (A), S11Q1.1 (G), S11Q2.3, S11R2.2, S11R3.2
unnamed: S11Q2.1, S11R1.1, S11R4.2
unnamed: S11R4.1, S11U2.1 (CATHODE)
unnamed: S11C3.2, S11R3.1, S11R5.2, S11R6.2, S11U2.2 (REF)
unnamed: S13D1.2 (A), S13R1.1
unnamed: S13D2.2 (A), S13R2.1
unnamed: S13D3.2 (A), S13R3.1
unnamed: S15C2.1, S15C3.1, S15C4.1, S15FB1.2, S15L1.1
unnamed: S15FB1.1, S15R1.1
unnamed: S15J3.1 (In), S15J4.1
unnamed: S16R3.2, S16U2.3 (RXD)
unnamed: S16R2.2, S16U2.2 (TXD)
unnamed: S18BT1.P, S18F1.1
unnamed: S18C1.1, S18F1.2, S18U1.1 (VIN)
unnamed: S19C11.1, S19R18.2
unnamed: S19C9.1, S19U5.12 (CAP)
unnamed: S19R19.2, S19R20.1, S19U5.8 (FB)
unnamed: S19R14.1, S19U5.6 (RT)
unnamed: S19L1.2, S19U5.1 (SW)
unnamed: S19C12.1, S19R18.1, S19U5.7 (VC)
unnamed: S19C13.1, S19U5.5 (VCC)
unnamed: S20R38.2, S20R39.2, S20U1.3 (IN+)
unnamed: S20C1.1, S20R32.2, S20R33.1, S20U1.4 (IN-)
unnamed: S20R38.1, S20U1.5 (REF)
unnamed: S21Q1.1 (G), S21R1.2, S21R2.1
unnamed: S21Q2.1 (G), S21R3.2, S21R4.1
PP3V3: S1J3.40 (Pin_1), S1R1.2, S1R2.2, S3C1.2, S3C2.2, S3U1.6 (VS), S4R3.1, S7C1.1, S7C3.1, S7C8.1, S7R7.2, S7U1.4 (IN), S7U2.4 (IN), S7U4.4 (IN), S8R1.1, S12TP3.1 (1_1), S16C1.1, S16U1.4 (IN), S17C1.1, S17R1.1, S17R2.1, S17R3.1, S17U1.8 (VCC), S22C1.1, S22R1.1, S22U1.1 (V_{CCI}), S22U1.3 (~RESET), S22U1.16 (V_{CCP})
PP3V3_CAN: S7C4.1, S7R3.1, S7U2.1 (OUT), S9C1.1, S9C4.1, S9C5.1, S9R1.1, S9R2.1, S9U1.3 (VDD), S9U2.14 (VDD), S12TP5.1 (1_1)
PP3V3_CAN_ST: S7R3.2, S7R4.2, S22U1.4 (P0)
PP3V3_GNSS: S15R1.2, S16C2.1, S16C3.1, S16C4.1, S16R4.1, S16TP1.1 (1_1), S16U1.1 (OUT), S16U2.7 (VCC_IO), S16U2.8 (VCC)
PP3V3_GNSS_BCKP: S7C2.1, S7R10.1, S7U1.1 (OUT), S12TP4.1 (1_1), S16C5.1, S16U2.6 (V_BCKP)
PP3V3_GNSS_BCKP_ST: S7R10.2, S7R11.2, S22U1.9 (P4)
PP3V3_GNSS_ST: S16R4.2, S16R5.1, S22U1.7 (P3)
PP3V3_K: S7C9.1, S7R8.1, S7U4.1 (OUT), S10R1.1, S10R2.1, S10R6.2, S12TP6.1 (1_1)
PP3V3_K_ST: S7R8.2, S7R9.2, S22U1.5 (P1)
PP4V2: S1C1.2, S1J4.1, S11C1.1, S11C2.1, S11U1.3 (~CE), S11U1.6 (VOUT), S12TP2.1 (1_1)
PP4V2_OVP_PROTECTED: S11Q1.3 (D), S11U1.1 (VIN)
PP4V2_UNPROTECTED: S6C4.2, S6C5.1, S6L1.2, S6R3.2, S6R6.1, S11D1.3 (K), S11Q1.2 (S), S11Q2.2, S11R1.2, S11R5.1
PP12V: S1J1.6, S2F2.1, S2R3.2, S20R32.1
PP12VI: S1J1.7, S2F1.2
PP12VIP: S2D1.3 (K), S2Q1.2 (S), S4R1.1
PP12VP: S2C1.1, S2C2.1, S2C3.1, S2D3.3 (K), S2D5.1 (K), S2Q2.1, S2Q2.2, S2Q2.3, S2Q3.2 (S), S3U1.8 (Vbus), S3U1.9 (Vin-), S3U1.10 (Vin+), S6C3.1, S6C8.1, S6R4.2, S6U1.9 (VIN), S7C6.1, S7U3.5 (VS_1), S7U3.6 (VS_2), S7U3.7 (VS_3), S7U3.8 (VS_4)
PP12V_K: S7C5.1, S7R5.1, S7U3.3 (OUT), S10C1.2, S10D1.2 (A), S10U1.7 (VBAT), S12TP7.1 (1_1)
PP12V_K_ST: S7C7.1, S7Q1.3 (D), S7R7.1, S22U1.6 (P2)
RF: S15C1.2, S15J2.1, S15L1.2
VBAT: S18U1.3 (~CE), S18U1.6 (VOUT), S19C7.1, S19C8.1, S19L1.1, S19U5.3 (VIN), S20C2.1, S20U1.6 (V+)
VBOOST: S2D5.2 (A), S2R4.1, S19C9.2, S19C14.1, S19C15.1, S19R19.1, S19U5.11 (VOUT)

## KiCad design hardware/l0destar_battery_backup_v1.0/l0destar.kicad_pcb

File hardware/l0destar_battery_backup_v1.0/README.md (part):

# l0destar battery backup v1.0

## Overview

**NOTE: THIS HAS NOT YET BEEN BUILT OR TESTED, USE AT YOUR OWN RISK**

- This is a prototype inline battery backup module for the l0destar vehicle
  tracker. It sits in the harness between the car and the tracker and holds
  the tracker's supply at ~9V from a single CR123A lithium primary cell when
  car power is cut
- It is designed to be hand-solderable (hot air required). Every active part
  is in a leaded package: MSOP-12, SOT-23, SC70, VSSOP-8, DPAK
- The cell is a **non-rechargeable** primary in a board-mounted holder.
  Nothing on the board charges it. See [Why a primary cell](#why-a-primary-cell)
- Pin-compatible with the v3.4 tracker's 2x3 Micro-Fit harness: J1 takes the
  car harness, J2 goes to the tracker, and the CAN/K-line and ignition pins pass
  straight through
- 4-layer 63.1 x 36.2 mm board, JLC04161H-7628 stack-up, four M2 mounting
  holes. Schematic ERC and PCB DRC are clean apart from the expected items
  listed under [Notes](#notes)

## Disclaimer

This is a prototype, not a product. Nothing here is validated or certified,
the parts lists are examples rather than a verified BOM, and every number
below is a desk calculation from datasheets rather than a bench measurement -
repeat the testing yourself rather than taking any of it on trust.

I strongly recommend not using unbranded CR123 cells or buying them from less
reputable sources.

**Before building or installing anything from this repository, read the
[full disclaimer](../../DISCLAIMER.md).**

## Test status

| Item | Test | Result | Notes |
|---------|------|--------|-------|
| Input stage | 12V car input reverse polarity | NOT TESTED | S1U1/S1Q1 ideal diode blocks; S1Z1 conducts forward into S1F1, which should clear |
| Input stage | Pass-through drop VCAR to PPTRACKER at 50 mA and 250 mA | NOT TESTED | Expected tens of mV through S1Q1 (27 mΩ), with brief body-diode drops while the LM74610 charge pump recharges |
| Input stage | ISO 7637-2 pulse 2a and 35V load dump ride-through | NOT TESTED | S1Z1 is the tracker's 33V TVS; S1C2 47 µF + S1C6 10 µF + S1C1 on VCAR |
| Switchover | Boost enables when the car rail falls below ~10.06V | NOT TESTED | S5U1 with the 6.8M/909k divider |
| Switchover | Boost disables when the car rail returns above ~11V | NOT TESTED | Depends on the cell voltage through S5R38/S5R39, see [Notes](#notes) |
| Switchover | PPTRACKER dip during handover under a forced LTE burst | NOT TESTED | Scope on J2 pin 4; S1C4 100 µF + S1C5 10 µF carry the gap |
| Boost | 9.6V output at S4C14/S4C15 | NOT TESTED | 1.202V x (1 + 909k/130k) = 9.61V; ~9V at J2 after S1D2 |
| Boost | Output current at a 2.5V cell | NOT TESTED | Burst Mode limits to ~190 mA at 2.5V in, ~300 mA at 3V in (datasheet curves) |
| Boost | Bode plot and load step | NOT TESTED | Compensation is the datasheet 2xAA to 12V example, not tuned for this operating point |
| Cell lockout | Boost held off below 2.45V, released above 2.52V | NOT TESTED | S5U4 with 1M/1M divider and 33M feedback; test on a bench supply in place of the cell |
| Cell lockout | Re-enable paced ~0.3 s | NOT TESTED | S5R41/S5C7; S5D1 makes the disable immediate |
| Cell | Reversed cell is harmless | NOT TESTED | S3U1 blocks, VBAT sits at 0V, no backup |
| Cell | No current ever flows into the cell | NOT TESTED | Ammeter in series with the cell with the car present and during handover |
| Wake pulse | IGN pulse at boost start | NOT TESTED | Expected ~12V peak, above 8V for ~0.4 s, at J2 pin 5 |
| Wake pulse | Sleeping tracker wakes and raises `backup power` | NOT TESTED | Needs firmware with `CONFIG_APP_BACKUP_SUPPLY=y` |
| Board | Idle draw from the cell, tracker asleep | NOT TESTED | Expected ~280 µA at a 2.9V cell |
| Board | Parked drain from the car with the cell fitted | NOT TESTED | Expected ~1.6 µA from the 7.7M sense divider on top of the tracker's own draw |
| Enclosure | Board and cell fit, lid clearance over the cell | NOT TESTED | 1.9 mm above the cell by the datasheet, see [enclosure/](enclosure/) |

## Features

 - Inline between the car harness and the tracker; CAN/K-line and ignition
   pass straight through
 - ~5-10uA quiescent current in pass-through operation (untested)
 - Same input protection parts as the tracker: 2A time-lag fuse, 33V TVS
   sized to ride out suppressed load dump
 - Reverse polarity protection
 - Synchronous boost (LTC3122) with true output disconnect: the backup rail
   is 0V while the car is present, so the cell is only ever loaded during a
   cut
 - Nanopower comparator switchover (2 x TLV3012, 2.8 µA each) running
   straight from the cell: takes over below ~10.06V on the car rail
 - Cell undervoltage lockout at 2.45V with a paced restart, so a tired cell
   is stopped a few percent above its rated end voltage rather than flattened
 - Ignition wake pulse: a cut wakes a sleeping tracker immediately instead of
   at its next timed wake, and the tracker reports the cut
 - Estimated runtime on a 1500 mAh CR123A: ~200 days idle, ~58 days
   reporting hourly, ~19 days reporting every 15 minutes
 - 3D-printable two-part enclosure with the cell accessible under the lid

## Why a primary cell

A non-rechargeable cell rather than a rechargeable pack, for three reasons:

- No rechargeable 18650-format cell is rated for storage in a sun-parked car.
  The binding limit is storage temperature (+45 °C at best for Li-ion and LFP;
  +20 °C beyond three months for LTO) and a parked car reaches ~70 °C cabin
  air. A CR123A is rated to +60/+70 °C
- Cycle life is not worth paying for. The backup cycles a handful of times a
  year
- A primary turns silent ageing into an event. The boost regulates its output,
  so the tracker cannot see cell voltage - a rechargeable's calendar fade would
  be invisible until a real theft tested it. The only thing that consumes a
  primary is a power cut the tracker already alerts on, so *"did it get
  used?"* is answered in the server's alert log

The cell is a consumable. A `backup power` alert that runs for a long time
means the cell needs replacing, since it does not recover. Taking the cell
out is the storage mode.

### Ignition wake pulse

A sleeping tracker has three wake sources: its timer, the accelerometer and
ignition-present. A power cut touches none of them, so on its own it would be
found at the next timed wake. The module therefore fakes ignition for a
moment when it takes over.

The tracker's wake is level-triggered and the firmware latches it, so the
pulse only has to trip the interrupt. On an ignition wake the firmware reads
the rail first: in the backup band it is the module's pulse, so the unit
reports at once with the `backup power` alert and goes back to sleep.

Limits: a second cut within the ~40 s VBOOST decay, or a cut with the key on
and the ignition wire loaded by the car, gives no pulse; both fall back to
the timed wake.

## Board configuration

### Connectors

Both connectors are the tracker's Molex Micro-Fit 3.0 2x3 (43045-0600) with
the v3.4 pinout. J1 is the car harness, J2 goes to the tracker.

| Pin | J1 (car) | J2 (tracker) | Notes |
|-----|----------|--------------|-------|
| 1 | SPARE | SPARE | Unused by v3.4, not connected on this board |
| 2 | GND | GND | |
| 3 | CAN\_H / K | CAN\_H / K | Passed straight through |
| 4 | +12V | +12V (PPTRACKER) | Car through the ideal diode, or ~9V from the boost on backup |
| 5 | IGN | IGN | Passed straight through; the wake pulse is injected here |
| 6 | CAN\_L / L | CAN\_L / L | Passed straight through |

### Firmware

The tracker needs `CONFIG_APP_BACKUP_SUPPLY=y`. With it, a supply between
`CONFIG_APP_BACKUP_MIN_MV` (8500) and `CONFIG_APP_BACKUP_MAX_MV` (9700) with
the ignition off is treated as backup power rather than a flat car battery:
timed reports keep going, the 11.8V power-off and 12.0V sleep-safety rules
are bypassed, a `backup power` alert is raised once and a `car power
restored` alert when the rail comes back. Without the module a car battery in
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
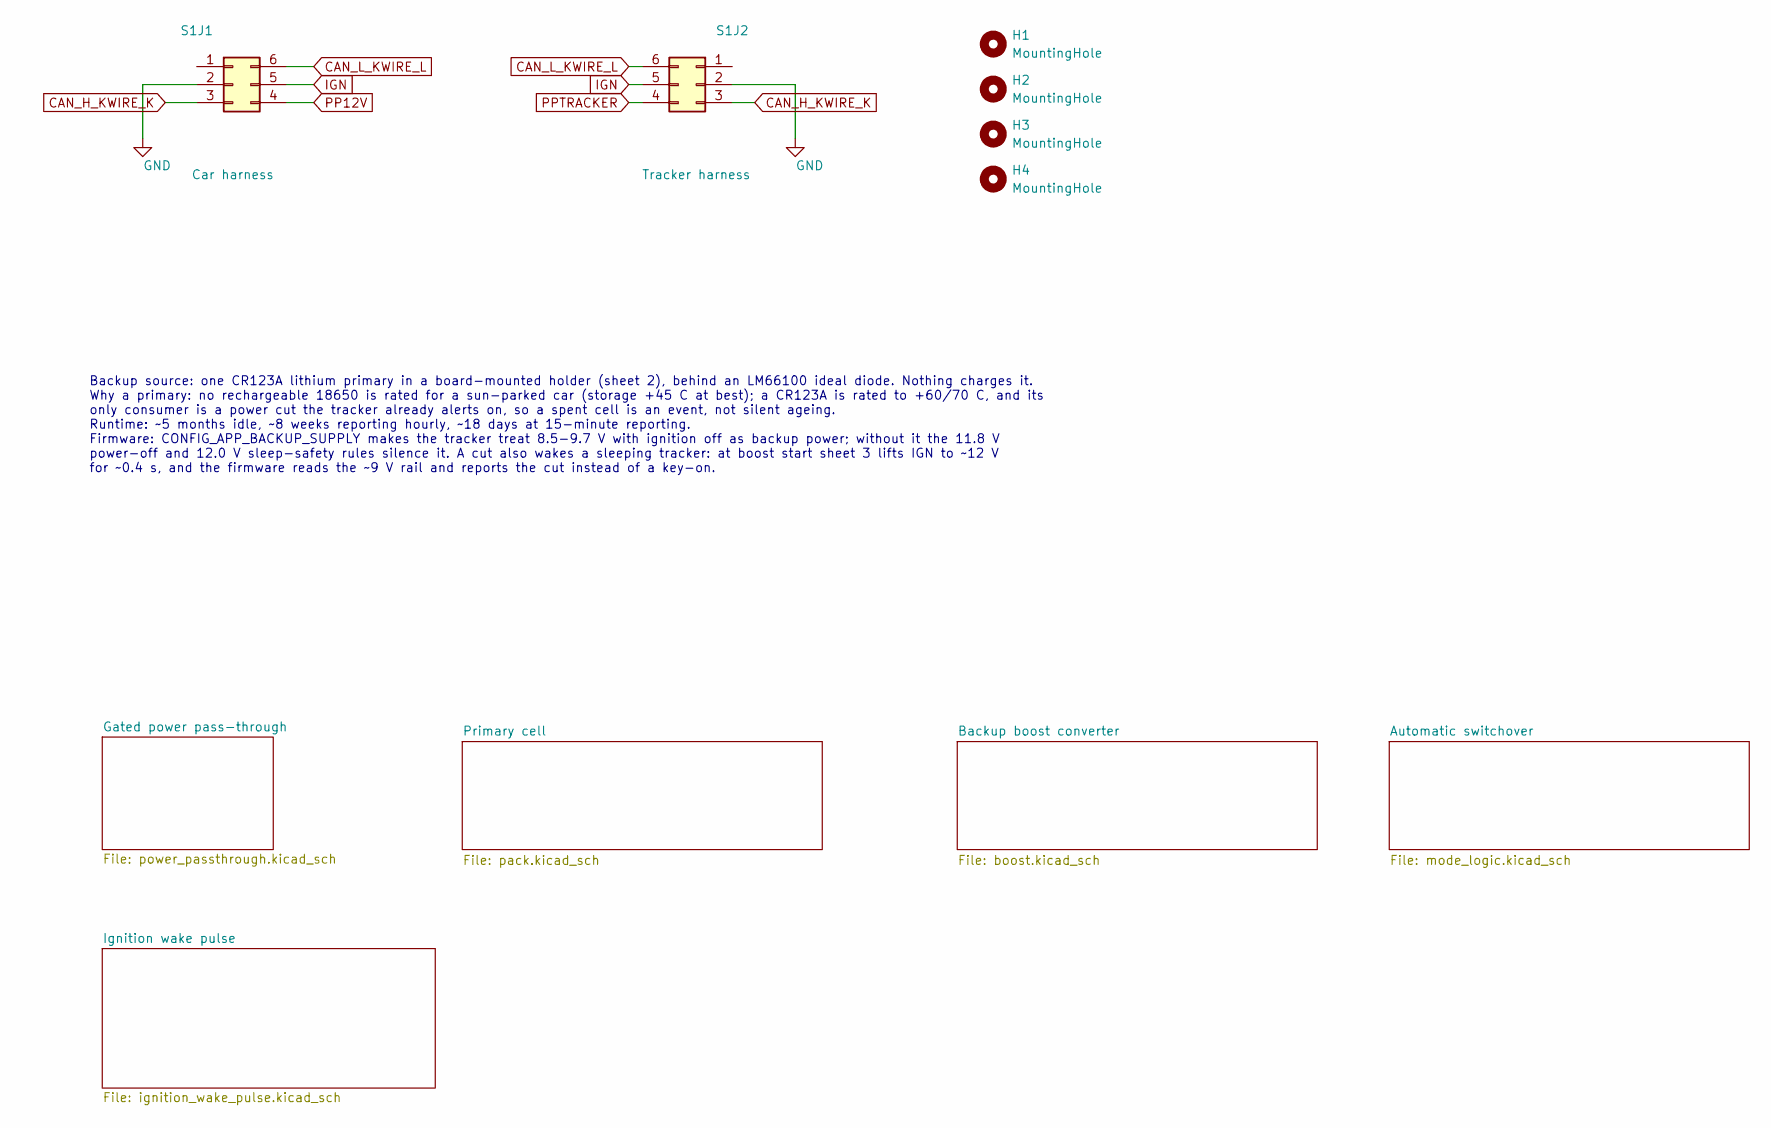
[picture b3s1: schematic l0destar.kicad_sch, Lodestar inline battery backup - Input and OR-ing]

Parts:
H1, H2, H3, H4: MountingHole; MountingHole_2.2mm_M2
S1J1: Car harness; Molex_Micro-Fit_3.0_43045-0600_2x03_P3.00mm_Horizontal
S1J2: Tracker harness; Molex_Micro-Fit_3.0_43045-0600_2x03_P3.00mm_Horizontal

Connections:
CAN_H_KWIRE_K: S1J1.3, S1J2.3
CAN_L_KWIRE_L: S1J1.6, S1J2.6
GND: S1J1.2, S1J2.2; also elsewhere on the board
IGN: S1J1.5, S1J2.5; also elsewhere on the board
PP12V: S1J1.4; also elsewhere on the board
PPTRACKER: S1J2.4; also elsewhere on the board

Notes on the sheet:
Backup source: one CR123A lithium primary in a board-mounted holder (sheet 2), behind an LM66100 ideal diode. Nothing charges it. Why a primary: no rechargeable 18650 is rated for a sun-parked car (storage +45 C at best); a CR123A is rated to +60/70 C, and its only consumer is a power cut the track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

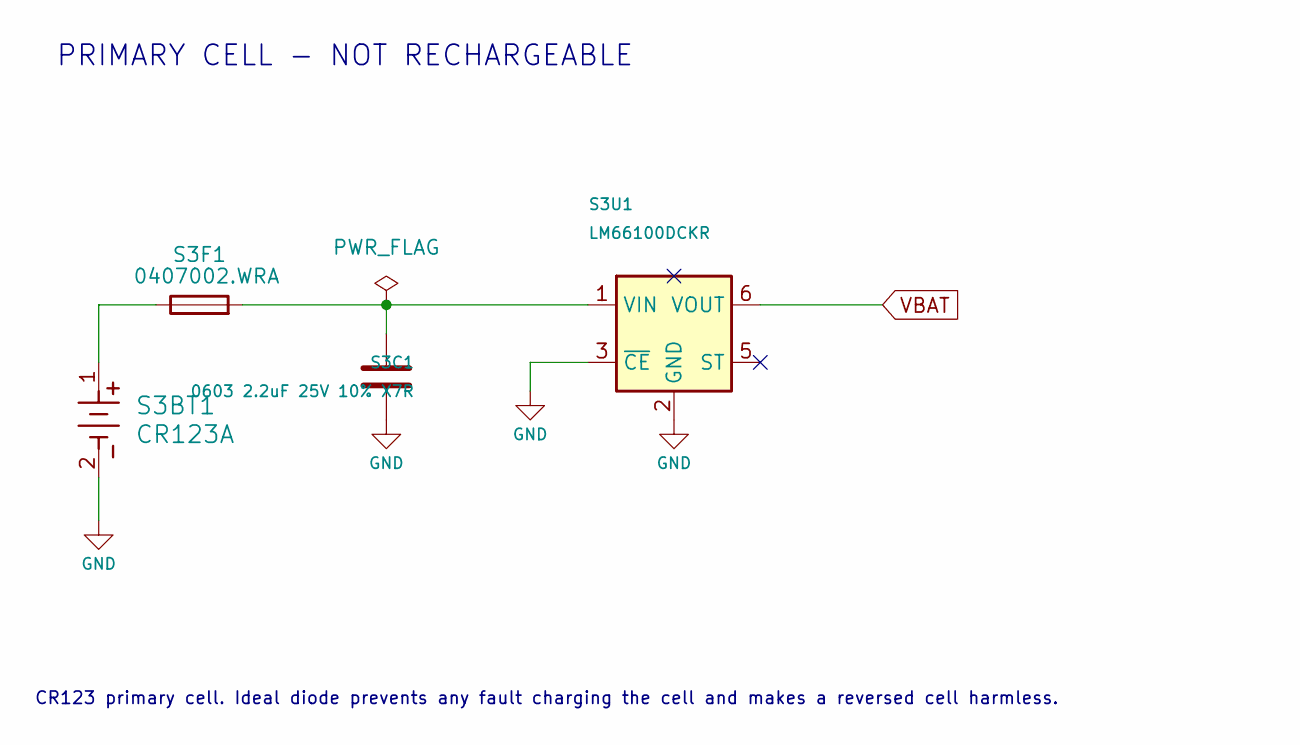
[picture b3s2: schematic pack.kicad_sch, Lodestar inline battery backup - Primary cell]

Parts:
S3BT1: CR123A; 1051_KEY; MPN 1051
S3C1: 0603 2.2uF 25V 10% X7R; C_0603_1608Metric; MPN GRM188Z71E225KE43D
S3F1: 0407002.WRA; Fuse_1206_3216Metric; MPN 0407002.WRA
S3U1: LM66100DCKR; SOT-363_SC-70-6; MPN LM66100DCKR

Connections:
GND: S3BT1.2, S3C1.2, S3U1.2 (GND), S3U1.3 (~CE); also elsewhere on the board
unnamed: S3BT1.1, S3F1.1
unnamed: S3C1.1, S3F1.2, S3U1.1 (VIN)
VBAT: S3U1.6 (VOUT); also elsewhere on the board

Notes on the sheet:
PRIMARY CELL - NOT RECHARGEABLE
CR123 primary cell. Ideal diode prevents any fault charging the cell and makes a reversed cell harmless.
